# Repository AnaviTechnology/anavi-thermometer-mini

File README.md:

# ANAVI Thermometer Mini

Tiny open source thermometer that supports communication over USB, Wi-Fi, BLE and Matter.

ANAVI Thermometer Mini has been designed with [the cross platform and open source electronics design automation suite KiCad](https://kicad.org/).

# License

The project is released under the [Creative Commons Attribution-ShareAlike 4.0 International (CC BY-SA 4.0)](https://creativecommons.org/licenses/by-sa/4.0/).

Note: This is a human-readable summary of (and not a substitute for) the [license](https://creativecommons.org/licenses/by-sa/4.0/legalcode).

You are free to:

Share — copy and redistribute the material in any medium or format Adapt — remix, transform, and build upon the material for any purpose, even commercially. The licensor cannot revoke these freedoms as long as you follow the license terms. Under the following terms:

Attribution — You must give appropriate credit, provide a link to the license, and indicate if changes were made. You may do so in any reasonable manner, but not in any way that suggests the licensor endorses you or your use. ShareAlike — If you remix, transform, or build upon the material, you must distribute your contributions under the same license as the original. No additional restrictions — You may not apply legal terms or technological measures that legally restrict others from doing anything the license permits. Notices:

You do not have to comply with the license for elements of the material in the public domain or where your use is permitted by an applicable exception or limitation. No warranties are given. The license may not give you all of the permissions necessary for your intended use. For example, other rights such as publicity, privacy, or moral rights may limit how you use the material.

You will have to provide a link to the original creator of the project http://www.anavi.technology on any documentation or website.

Credit can be attributed through a link to the creator website: http://www.anavi.technology

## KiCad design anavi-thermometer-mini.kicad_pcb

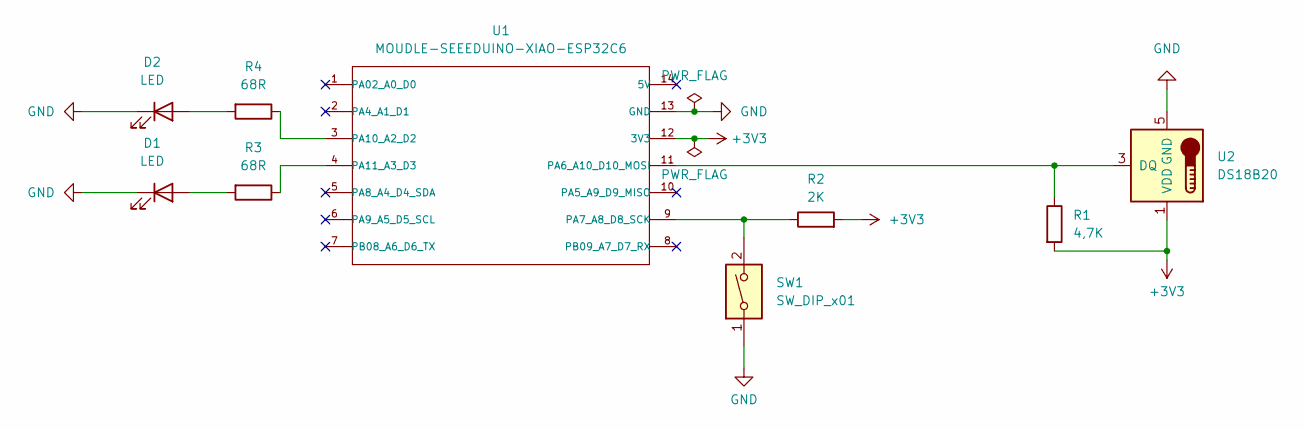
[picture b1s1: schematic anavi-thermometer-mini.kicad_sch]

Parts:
D1, D2: LED; LED_1206_3216Metric
R1: 4,7K; R_0603_1608Metric_Pad0.98x0.95mm_HandSolder
R2: 2K; R_0603_1608Metric_Pad0.98x0.95mm_HandSolder
R3, R4: 68R; R_0603_1608Metric_Pad0.98x0.95mm_HandSolder
SW1: SW_DIP_x01; SW_PUSH_6mm_H4.3mm
U1: MOUDLE-SEEEDUINO-XIAO-ESP32C6; MOUDLE14P-SMD-2.54-21X17.8MM
U2: DS18B20; CONN3_2059-303&slash_998-403_WAG

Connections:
+3V3: R1.2, R2.2, U1.12 (3V3), U2.1 (VDD)
GND: D1.1 (K), D2.1 (K), SW1.1, U1.13 (GND), U2.5 (GND)
unnamed: D1.2 (A), R3.2
unnamed: D2.2 (A), R4.2
unnamed: R1.1, U1.11 (PA6_A10_D10_MOSI), U2.3 (DQ)
unnamed: R2.1, SW1.2, U1.9 (PA7_A8_D8_SCK)
unnamed: R4.1, U1.3 (PA10_A2_D2)
unnamed: R3.1, U1.4 (PA11_A3_D3)

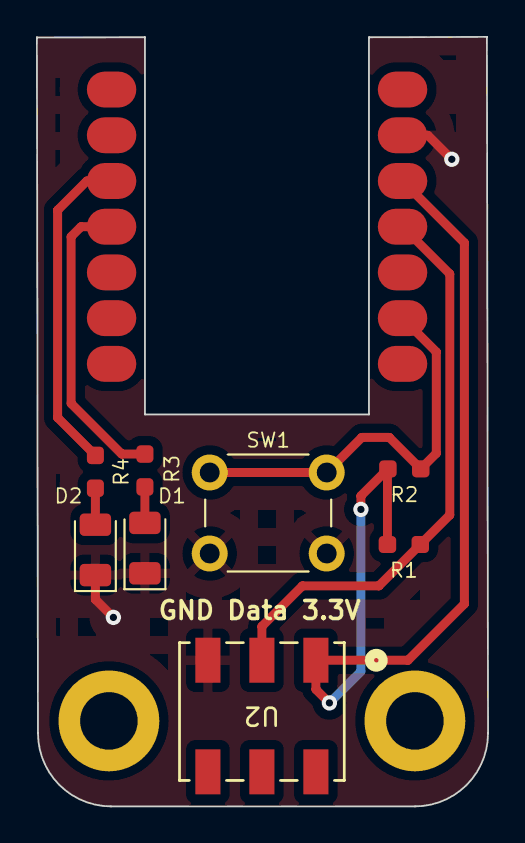
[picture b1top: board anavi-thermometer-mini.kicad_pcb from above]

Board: 2 copper layers, 25.1 x 42.8 mm, 9 parts (0 on the bottom side), 8 nets.

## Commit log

2025-04-26 ANAVI Thermometer Mini
    Initial commit
2025-04-26 anavi-thermometer-mini.kicad_pcb: PCB routing
    Adjust PCB routing.
2025-04-29 Minor adjustments of the PCB
2025-06-19 Fix mounting hole pad numbering
    Correct pad numbering for mounting holes in PCB Editor.
2025-11-28 Use WAGO 2059-303
    Replace the three screw terminal block with the more compact
    alternative WAGO 2059-303.

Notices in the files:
anavi-thermometer-mini.kicad_pcb:
(c) 2025
